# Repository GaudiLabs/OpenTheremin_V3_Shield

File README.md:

# OpenTheremin_V3_Shield
Open Source Theremin Instrument

Schematics, printed circuit board (PCB) design, bill of materials (BOM) for the Open.Theremin.V3 arduino shield.
For software see separate git repository.

### Don't click on the files!
Click on the "Download ZIP" Button to the right or [Click here](https://github.com/GaudiLabs/OpenTheremin_V3_Shield/archive/master.zip) 
Then unpack the archive.

### Open Source Theremin based on the Arduino Platform

Open.Theremin.V3 is an arduino shield to build the legendary music instrument invented by Leon Theremin back in 1920. The theremin is played with two antennas, one to control the pitch and one for volume. The electronic shield with two ports to connect those antennas comprises two heterodyne oscillators to measure the distance of the hand to the antenna when playing the instrument. The resulting signal is fed into the arduino. After linearization and filtering the arduino generates the instruments sound that is then played through a high quality digital analog audio converter on the board. The characteristics of the sound can be determined by a wave table on the arduino.

For more info on the open source project and on availability of ready made shield see:

http://www.gaudi.ch/OpenTheremin/

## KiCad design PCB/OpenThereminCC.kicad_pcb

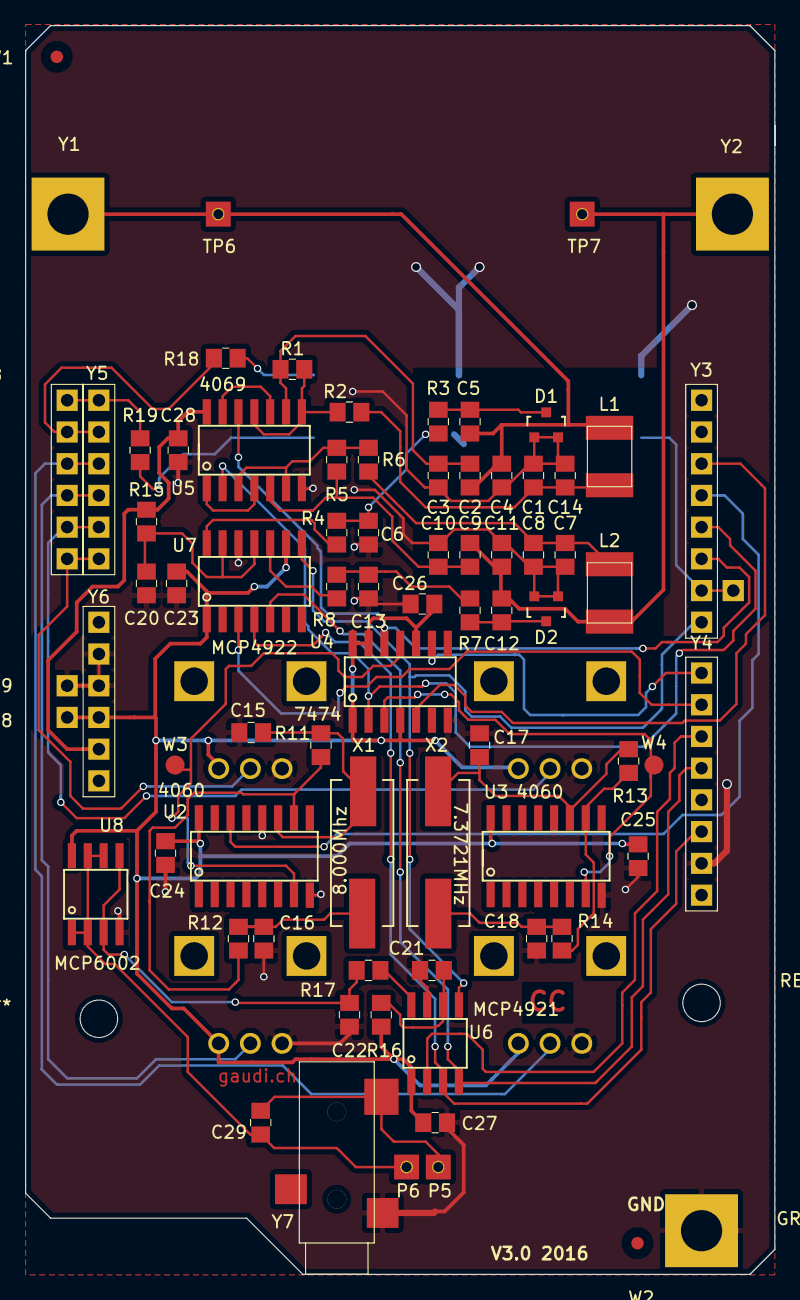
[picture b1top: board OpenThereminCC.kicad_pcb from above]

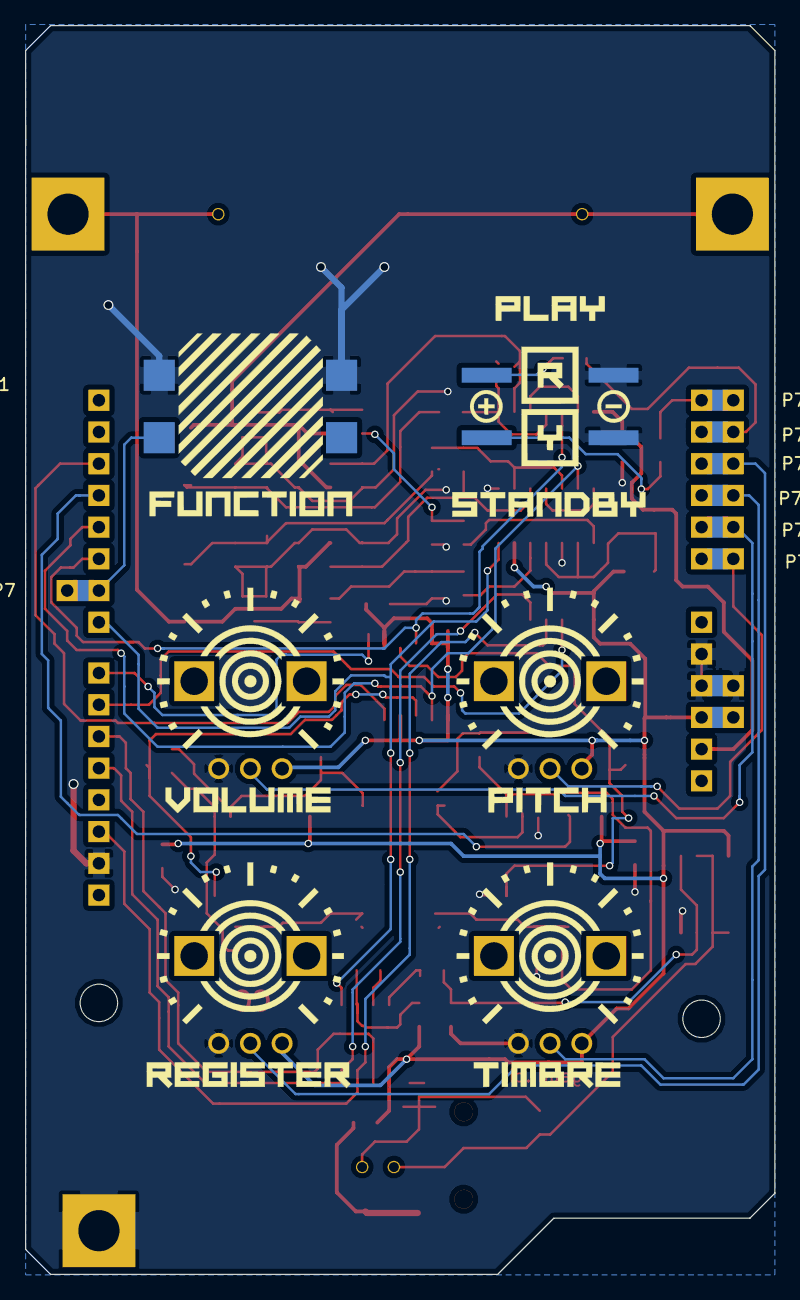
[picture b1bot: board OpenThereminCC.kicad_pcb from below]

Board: 2 copper layers, 60.0 x 100.0 mm, 95 parts (17 on the bottom side), 52 nets.

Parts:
C1: 220pF 270pF?; 0805G
C2, C3, C9, C10: 150pF; 0805G
C4: 15nF?; 0805G
C5, C12: 470pF; 0805G
C6, C13, C23, C24, C25, C26, C27, C28: 100nF; 0805G
C7, C14: ?pF; 0805G
C8: 330pF; 0805G
C11: 0; 0805G
C15, C16, C17, C18: 33pF; 0805G
C20, C21: 100n; 0805G
C22: 10n; 0805G
C29: 10uF; 0805G
D1, D2: BB914; SOT-23
D3, D4: LED; LED_SQUARE_5mm
GROUND1: GND_PAD; MountPad3
L1, L2: 1mH; COIL
P1, P2, P3, P4: 10k; POT
P5: SP+; MeasurePad_Square_wHole_2mm
P6: SP-; MeasurePad_Square_wHole_2mm
P7, P7#3, P7#4, P7#5, P7#6, P7#7, P7#8, P7#9, P7#10: CONN_01X01; SMD_Pinheader_1_OT_BLANK
P7#2, P8, P9: CONN_01X01; SMD_Pinheader_1_OT
R1, R5, R11, R13: 4.7M; 0805G
R2, R6, R17: 2.2k; 0805G
R3, R4, R7, R8, R15, R16: 100k; 0805G
R12, R14, R18, R19: 470; 0805G
SW1: SW_PUSH; PUSH_BUTTON_TL3300D
TP6: PITCH ANTENNA; MeasurePad_Square_wHole_2mm
TP7: VOLUME ANTENNA; MeasurePad_Square_wHole_2mm
U1: Arduino_UNO_R2; ArduinoUNO
U2, U3: 4060; SOIC-16_N
U4: 74HC74; SOIC-14_N
U5: 4069; SOIC-14_N
U6: MCP4921-E/SN; SOIC-08_N
U7: MCP4922-E/SL; SOIC-14_N
U8: LM358 / MCP6002; SOIC-08_N
W1: FIDUCIAL1; Fiducial_1mm_Dia_2.54mm_Outer_CopperTop
W2: FIDUCIAL2; Fiducial_1mm_Dia_2.54mm_Outer_CopperTop
W3: TP1; Measurement_Point_Round-SMD-Pad_Small
W4: TP2; Measurement_Point_Round-SMD-Pad_Small
X1: 8MHz; Crystal_HC49-SD_SMD
X2: 7.3721MHz; Crystal_HC49-SD_SMD
Y1, Y2: MountPad3
Y3, Y4: CONN_01X08; SMD_Pinheader_8_OT
Y5, Y6, Y8: CONN_01X06; SMD_Pinheader_6_OT
Y7: PLUG_3_5_SMD; PLUG3_5_SwitchCraft_2B

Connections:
A0: P1.2, Y5.6, Y8.6
A1: P2.2, Y5.5, Y8.5
A2: P3.2, Y5.4, Y8.4
A3: P4.2, Y5.3, Y8.3
BUT: P7#2.1, SW1.1, Y3.7
DAC2_CS: U7.3, Y4.2
DAC_CS: U6.2, Y4.3
DAC_DI: U6.4, U7.5, Y4.4
DAC_LATCH: U6.5, U7.8, Y3.8
DAC_SCK: U6.3, U7.4, Y4.6
F_PITCH: U4.9, Y4.1
F_VOL: U4.5, Y3.3
GND: C1.2, C3.2, C4.2, C6.2, C7.2, C8.2, C10.2, C11.2, C13.2, C14.2, C15.2, C16.2, C17.2, C18.2, C20.2, C21.2, C22.2, C23.2, C24.2, C25.2, C26.2, C27.2, C28.2, D1.1, D1.2, D2.1, D2.2, D3.1, D4.1, GROUND1.1, P1.1, P2.1, P3.1, P4.1, P9.1, SW1.2, U2.8, U2.12, U3.8, U3.12, U4.7, U5.7, U6.7, U7.12, U8.4, Y4.7, Y6.2, Y6.3, Y7.1
LED_GREEN: R18.2, Y5.2, Y8.2
LED_RED: R19.2, Y5.1, Y8.1
unnamed: C1.1, C14.1, L1.2, R2.1
unnamed: C2.1, C4.1, C5.1, L1.1, TP6.1, Y1.1
unnamed: C2.2, C3.1, R1.2, U5.9
unnamed: C5.2, D1.3, R3.2
unnamed: C6.1, R3.1, R4.1
unnamed: C7.1, C8.1, L2.2, R6.1
unnamed: C9.2, C10.1, R5.2, U5.5
unnamed: C9.1, C11.1, C12.1, L2.1, TP7.1, Y2.1
unnamed: C12.2, D2.3, R7.2
unnamed: C13.1, R7.1, R8.1
unnamed: C15.1, R11.2, U2.11, X1.1
unnamed: C16.1, R12.1, X1.2
unnamed: C17.1, R13.2, U3.11, X2.1
unnamed: C18.1, R14.1, X2.2
unnamed: C21.1, R16.1, U6.6
unnamed: C22.1, R17.2, U8.3, U8.5
unnamed: C29.1, P6.1, U8.1, U8.2, U8.6, U8.7
unnamed: C29.2, P5.1, Y7.3
unnamed: D3.2, R18.1
unnamed: D4.2, R19.1
unnamed: R1.1, R2.2, U5.8, U5.11
unnamed: R4.2, U7.14
unnamed: R5.1, R6.2, U5.3, U5.6
unnamed: R11.1, R12.2, U2.10
unnamed: R13.1, R14.2, U3.10
unnamed: R17.1, U6.8
unnamed: U2.7, U4.11, W3.1
unnamed: U3.7, U4.3, W4.1
unnamed: U5.1, U5.4
unnamed: U5.10, U5.13
SAMPLE_CLK: U2.14, Y3.4
VCC: C23.1, C24.1, C25.1, C26.1, C27.1, P1.3, P2.3, P3.3, P4.3, P8.1, R16.2, U2.16, U3.16, U4.1, U4.4, U4.10, U4.13, U4.14, U6.1, U7.1, U7.9, U8.8, Y6.4
VDD: C28.1, R15.2, U5.14, Y6.5
VO_PITCH: U4.12, U5.12, Y3.6
VO_VOL: U4.2, U5.2, Y3.5
VoutB: R8.2, U7.10
VrefB: C20.1, R15.1, U7.11, U7.13

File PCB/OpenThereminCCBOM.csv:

"Id";"Designator";"Package";"Quantity";"Designation";"Supplier and ref";
1;"L1,L2";"COIL";2;"1mH";;;
2;"P1,P2,P3,P4";"POT";4;"10k";;;
3;"X1";"Crystal_HC49-SD_SMD";1;"8MHz";;;
4;"X2";"Crystal_HC49-SD_SMD";1;"7.3721MHz";;;
5;"Y1,Y2";"MountPad3";2;"MountPad3";;;
6;"Y3,Y4";"SMD_Pinheader_8";2;"CONN_01X08";;;
7;"Y7";"PLUG3_5_SMD";1;"PLUG_3_5_SMD";;;
8;"Y5,Y6";"SMD_Pinheader_6";2;"CONN_01X06";;;
9;"D1,D2";"SOT-23";2;"BB914";;;
10;"SW1";"SW_PUSH_6mm";1;"SW_PUSH";;;
11;"D3,D4";"LED-0603";2;"LED";;;
12;"REF**,REF**";"MountingHoleRound3mm";2;"MountingHoleRound3mm";;;
13;"R7,R16,R15,R8,R4,R3";"0805G";6;"100k";;;
14;"R19,R18";"0805G";2;"390";;;
15;"C28,C27,C26,C25,C24,C23,C13,C6";"0805G";8;"100nF";;;
16;"R17";"0805G";1;"2.2k";;;
17;"C22";"0805G";1;"10n";;;
18;"C21,C20";"0805G";2;"100n";;;
19;"C19,C18,C17,C16,C15,C11,C4";"0805G";7;"33pF";;;
20;"C14,C7";"0805G";2;"1n";;;
21;"C12,C5";"0805G";2;"83pF";;;
22;"C10,C9,C3,C2";"0805G";4;"50pF";;;
23;"C8,C1";"0805G";2;"330pF";;;
24;"R14,R12";"0805G";2;"470";;;
25;"R13,R11,R5,R1";"0805G";4;"4.7M";;;
26;"R10,R9,R20";"0805G";3;"4.7k";;;
27;"R6,R2";"0805G";2;"10k";;;
28;"C29";"0805G";1;"CP_Small";;;
29;"U7";"SOIC-14_N";1;"MCP4922-E/SL";;;
30;"U4";"SOIC-14_N";1;"74HC74";;;
31;"U5";"SOIC-14_N";1;"4069";;;
32;"U2,U3";"SOIC-16_N";2;"4060";;;
33;"U6";"SOIC-08_N";1;"MCP4921-E/SN";;;
34;"U8";"SOIC-08_N";1;"LM358 / MCP6002";;;
35;"U1";"ArduinoUNO";1;"Arduino_UNO_R2";;;
36;"G***";"Theremin_Roy1";1;"LOGO";;;
37;"G***";"OpenHardwareLogo";1;"LOGO";;;
38;"R21";"0805G";1;"47K";;;
39;"R22";"0805G";1;"100K";;;
40;"U9";"SOIC-08_N";1;"LM385";;;
41;"TP5";"PAD_SMD_3mm";1;"VREF";;;
42;"G***";"SGMKLogo";1;"LOGO";;;
43;"G***";"Peace_logo";1;"LOGO";;;
44;"REF**,REF**";"Fiducial_1mm_Dia_2.54mm_Outer_CopperTop";2;"Fiducial_1mm_Dia_2.54mm_Outer_CopperTop";;;
45;"GROUND1";"MeasurePad_Square_wHole_2mm";1;"GND_PAD";;;
46;"TP7";"MeasurePad_Square_wHole_2mm";1;"VOLUME ANTENNA";;;
47;"TP6";"MeasurePad_Square_wHole_2mm";1;"PITCH ANTENNA";;;
48;"P6";"MeasurePad_Square_wHole_2mm";1;"SP-";;;
49;"P5";"MeasurePad_Square_wHole_2mm";1;"SP+";;;
50;"TP4";"MeasurePad_Square_wHole_2mm";1;"F_VOL";;;
51;"TP3";"MeasurePad_Square_wHole_2mm";1;"F_PITCH";;;
52;"TP2";"MeasurePad_Square_wHole_2mm";1;"VO_VOL";;;
53;"TP1";"MeasurePad_Square_wHole_2mm";1;"VO_PITCH";;;

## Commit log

2016-09-21 Secont prototype of Version 3 PCB
    Now testing...
2017-01-17 Update batch 2, OSHW certificate, CV instruction
2020-09-03 typo: v3 readme referenced v1 "download zip"
